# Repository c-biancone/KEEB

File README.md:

# KEEB

SOLIDWORKS and KiCAD fiels for a custom keyboard I hope to build.

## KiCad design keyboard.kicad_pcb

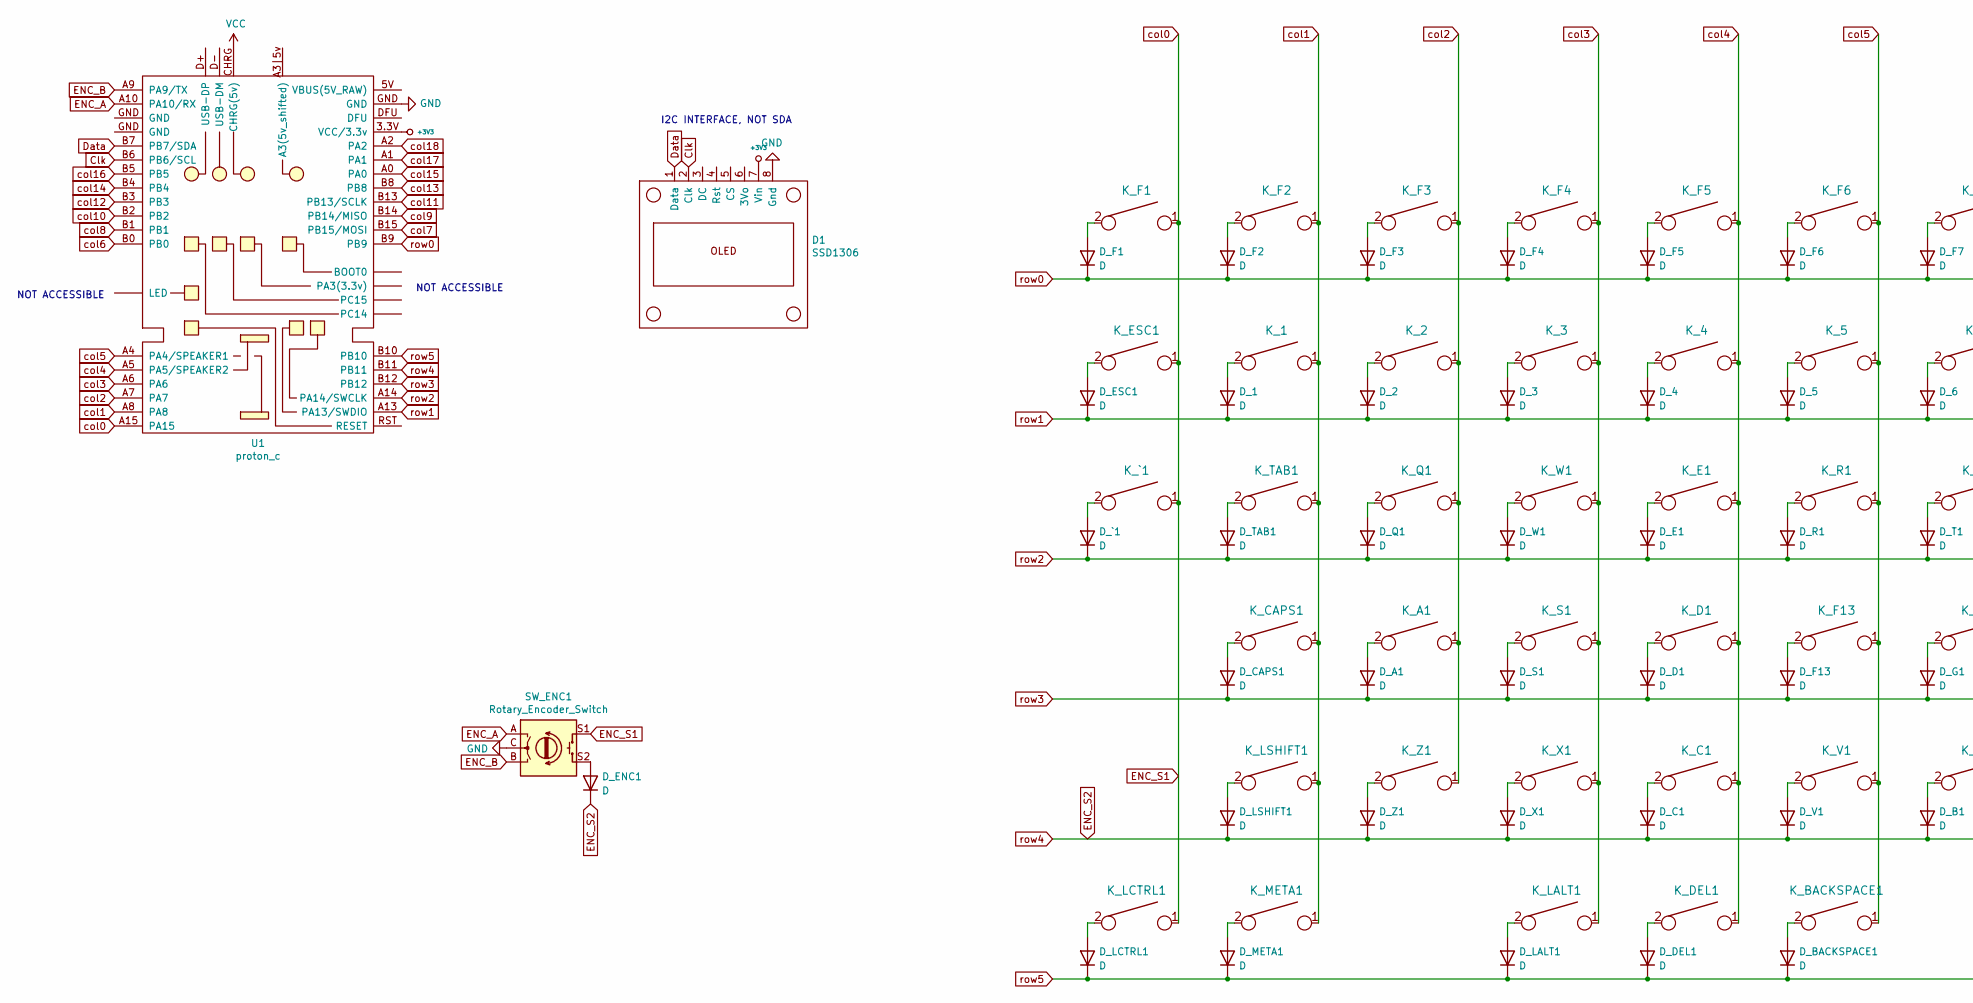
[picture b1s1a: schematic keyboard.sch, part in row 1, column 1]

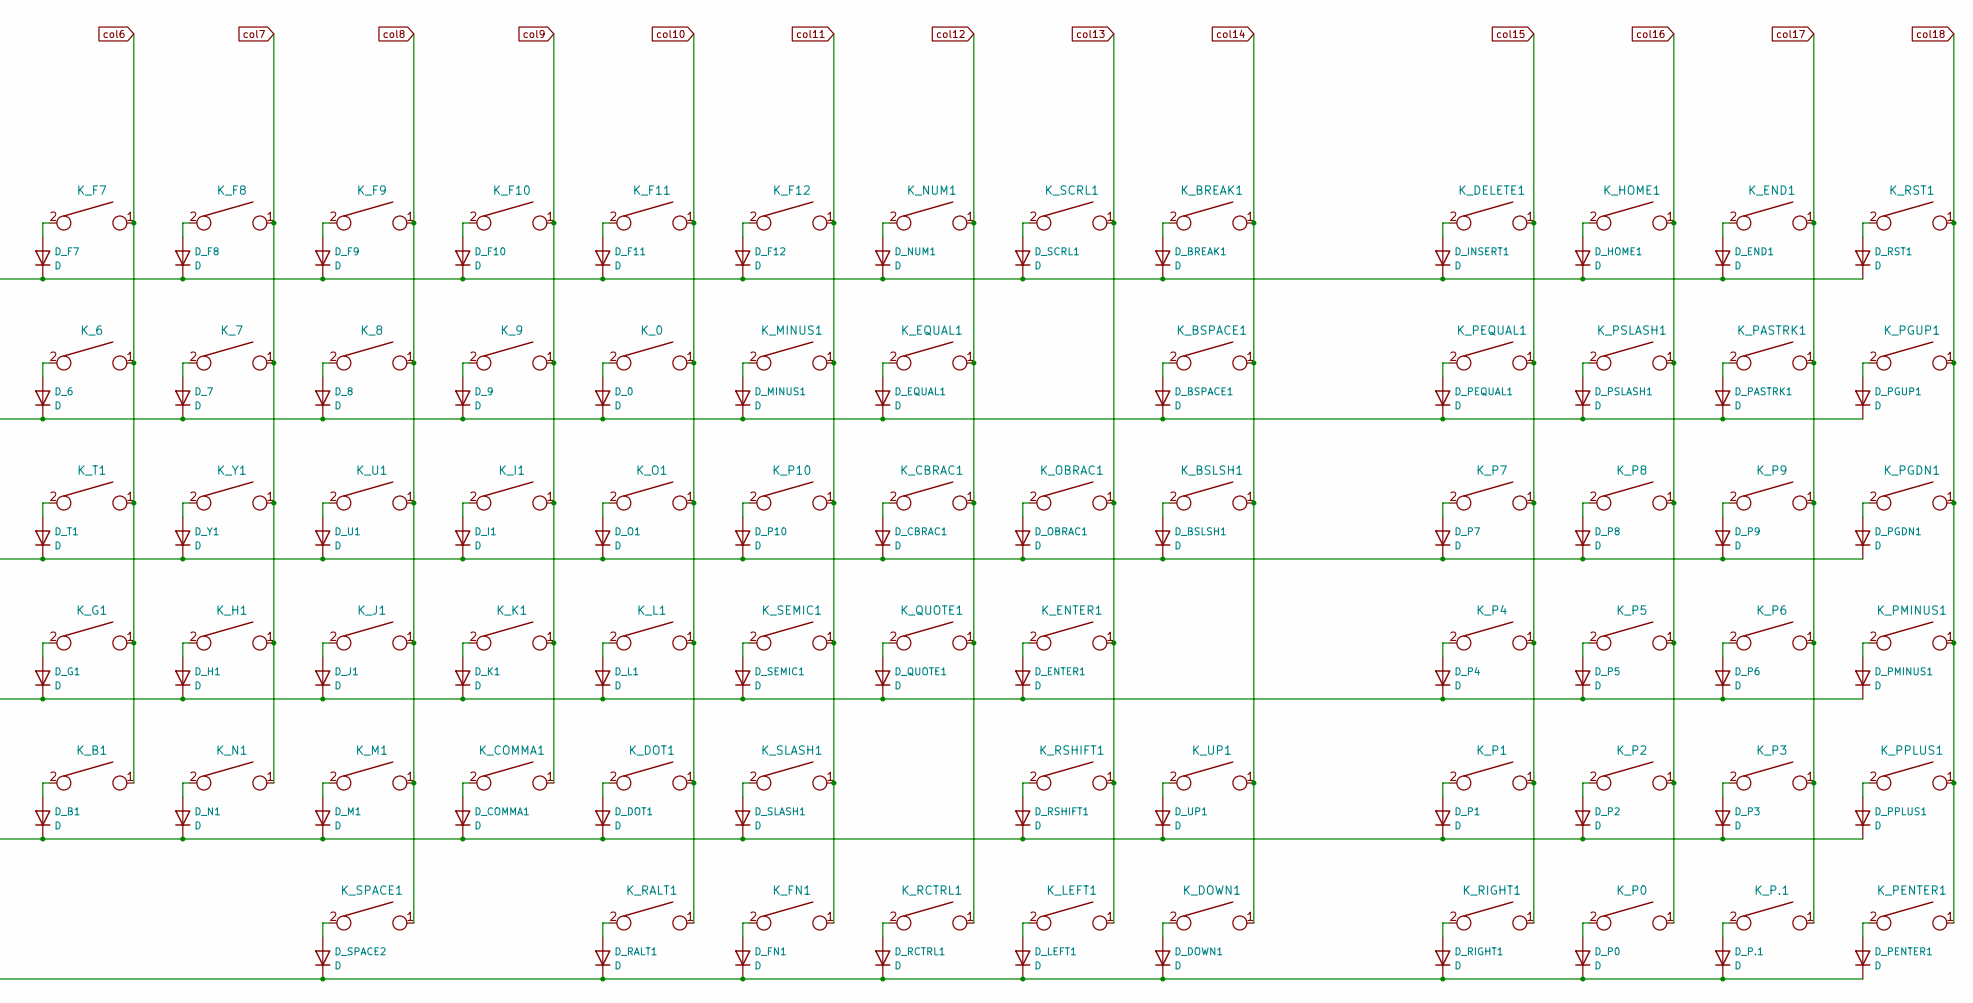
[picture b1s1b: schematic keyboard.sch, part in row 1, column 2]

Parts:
D1: SSD1306; MOUNTINGHOLE_2.5_PLATED
D_0, D_1, D_2, D_3, D_4, D_5, D_6, D_7, D_8, D_9: D; D_SOD123_axial
D_A1: D; D_SOD123_axial
D_B1: D; D_SOD123_axial
D_BACKSPACE1: D; D_SOD123_axial
D_BREAK1: D; D_SOD123_axial
D_BSLSH1: D; D_SOD123_axial
D_BSPACE1: D; D_SOD123_axial
D_C1: D; D_SOD123_axial
D_CAPS1: D; D_SOD123_axial
D_CBRAC1: D; D_SOD123_axial
D_COMMA1: D; D_SOD123_axial
D_D1: D; D_SOD123_axial
D_DEL1: D; D_SOD123_axial
D_DOT1: D; D_SOD123_axial
D_DOWN1: D; D_SOD123_axial
D_E1: D; D_SOD123_axial
D_ENC1: D; D_SOD123_axial
D_END1: D; D_SOD123_axial
D_ENTER1: D; D_SOD123_axial
D_EQUAL1: D; D_SOD123_axial
D_ESC1: D; D_SOD123_axial
D_F1, D_F2, D_F3, D_F4, D_F5, D_F6, D_F7, D_F8, D_F9, D_F10, D_F11, D_F12, D_F13: D; D_SOD123_axial
D_FN1: D; D_SOD123_axial
D_G1: D; D_SOD123_axial
D_H1: D; D_SOD123_axial
D_HOME1: D; D_SOD123_axial
D_I1: D; D_SOD123_axial
D_INSERT1: D; D_SOD123_axial
D_J1: D; D_SOD123_axial
D_K1: D; D_SOD123_axial
D_L1: D; D_SOD123_axial
D_LALT1: D; D_SOD123_axial
D_LCTRL1: D; D_SOD123_axial
D_LEFT1: D; D_SOD123_axial
D_LSHIFT1: D; D_SOD123_axial
D_M1: D; D_SOD123_axial
D_META1: D; D_SOD123_axial
D_MINUS1: D; D_SOD123_axial
D_N1: D; D_SOD123_axial
D_NUM1: D; D_SOD123_axial
D_O1: D; D_SOD123_axial
D_OBRAC1: D; D_SOD123_axial
D_P0, D_P1, D_P2, D_P3, D_P4, D_P5, D_P6, D_P7, D_P8, D_P9, D_P10, D_P.1: D; D_SOD123_axial
D_PASTRK1: D; D_SOD123_axial
D_PENTER1: D; D_SOD123_axial
D_PEQUAL1: D; D_SOD123_axial
D_PGDN1: D; D_SOD123_axial
D_PGUP1: D; D_SOD123_axial
D_PMINUS1: D; D_SOD123_axial
D_PPLUS1: D; D_SOD123_axial
D_PSLASH1: D; D_SOD123_axial
D_Q1: D; D_SOD123_axial
D_QUOTE1: D; D_SOD123_axial
D_R1: D; D_SOD123_axial
D_RALT1: D; D_SOD123_axial
D_RCTRL1: D; D_SOD123_axial
D_RIGHT1: D; D_SOD123_axial
D_RSHIFT1: D; D_SOD123_axial
D_RST1: D; D_SOD123_axial
D_S1: D; D_SOD123_axial
D_SCRL1: D; D_SOD123_axial
D_SEMIC1: D; D_SOD123_axial
D_SLASH1: D; D_SOD123_axial
D_SPACE2: D; D_SOD123_axial
D_T1: D; D_SOD123_axial
D_TAB1: D; D_SOD123_axial
D_U1: D; D_SOD123_axial
D_UP1: D; D_SOD123_axial
D_V1: D; D_SOD123_axial
D_W1: D; D_SOD123_axial
D_X1: D; D_SOD123_axial
D_Y1: D; D_SOD123_axial
D_Z1: D; D_SOD123_axial
D_`1: D; D_SOD123_axial
K_0, K_1, K_2, K_3, K_4, K_5, K_6, K_7, K_8, K_9: KEYSW; MX-1U-NoLED
K_A1: KEYSW; MX-1U-NoLED
K_B1: KEYSW; MX-1U-NoLED
K_BACKSPACE1: KEYSW; MX-2U-NoLED
K_BREAK1: KEYSW; MX-1U-NoLED
K_BSLSH1: KEYSW; MX-1.5U-NoLED
K_BSPACE1: KEYSW; MX-2U-NoLED
K_C1: KEYSW; MX-1U-NoLED
K_CAPS1: KEYSW; MX-1.75U-NoLED
K_CBRAC1: KEYSW; MX-1U-NoLED
K_COMMA1: KEYSW; MX-1U-NoLED
K_D1: KEYSW; MX-1U-NoLED
K_DEL1: KEYSW; MX-1U-NoLED
K_DELETE1: KEYSW; MX-1U-NoLED
K_DOT1: KEYSW; MX-1U-NoLED
K_DOWN1: KEYSW; MX-1U-NoLED
K_E1: KEYSW; MX-1U-NoLED
K_END1: KEYSW; MX-1U-NoLED
K_ENTER1: KEYSW; MX-2.25U-NoLED
K_EQUAL1: KEYSW; MX-1U-NoLED
K_ESC1: KEYSW; MX-1U-NoLED
K_F1, K_F2, K_F3, K_F4, K_F5, K_F6, K_F7, K_F8, K_F9, K_F10, K_F11, K_F12, K_F13: KEYSW; MX-1U-NoLED
K_FN1: KEYSW; MX-1.25U-NoLED
K_G1: KEYSW; MX-1U-NoLED
K_H1: KEYSW; MX-1U-NoLED
K_HOME1: KEYSW; MX-1U-NoLED
K_I1: KEYSW; MX-1U-NoLED
K_J1: KEYSW; MX-1U-NoLED
K_K1: KEYSW; MX-1U-NoLED
K_L1: KEYSW; MX-1U-NoLED
K_LALT1: KEYSW; MX-1.25U-NoLED
K_LCTRL1: KEYSW; MX-1.25U-NoLED
K_LEFT1: KEYSW; MX-1U-NoLED
K_LSHIFT1: KEYSW; MX-2.25U-NoLED
K_M1: KEYSW; MX-1U-NoLED
K_META1: KEYSW; MX-1.25U-NoLED
K_MINUS1: KEYSW; MX-1U-NoLED
K_N1: KEYSW; MX-1U-NoLED
K_NUM1: KEYSW; MX-1U-NoLED
K_O1: KEYSW; MX-1U-NoLED
K_OBRAC1: KEYSW; MX-1U-NoLED
K_P0, K_P1, K_P2, K_P3, K_P4, K_P5, K_P6, K_P7, K_P8, K_P9, K_P10, K_P.1: KEYSW; MX-1U-NoLED
K_PASTRK1: KEYSW; MX-1U-NoLED
K_PENTER1: KEYSW; MX-2U-NoLED
K_PEQUAL1: KEYSW; MX-1U-NoLED
K_PGDN1: KEYSW; MX-1U-NoLED
K_PGUP1: KEYSW; MX-1U-NoLED
K_PMINUS1: KEYSW; MX-1U-NoLED
K_PPLUS1: KEYSW; MX-1U-NoLED
K_PSLASH1: KEYSW; MX-1U-NoLED
K_Q1: KEYSW; MX-1U-NoLED
K_QUOTE1: KEYSW; MX-1U-NoLED
K_R1: KEYSW; MX-1U-NoLED
K_RALT1: KEYSW; MX-1U-NoLED
K_RCTRL1: KEYSW; MX-1.25U-NoLED
K_RIGHT1: KEYSW; MX-1U-NoLED
K_RSHIFT1: KEYSW; MX-1.75U-NoLED
K_RST1: KEYSW; MX-1U-NoLED
K_S1: KEYSW; MX-1U-NoLED
K_SCRL1: KEYSW; MX-1U-NoLED
K_SEMIC1: KEYSW; MX-1U-NoLED
K_SLASH1: KEYSW; MX-1U-NoLED
K_SPACE1: KEYSW; MX-2.75U-NoLED
K_T1: KEYSW; MX-1U-NoLED
K_TAB1: KEYSW; MX-1.5U-NoLED
K_U1: KEYSW; MX-1U-NoLED
K_UP1: KEYSW; MX-1U-NoLED
K_V1: KEYSW; MX-1U-NoLED
K_W1: KEYSW; MX-1U-NoLED
K_X1: KEYSW; MX-1U-NoLED
K_Y1: KEYSW; MX-1U-NoLED
K_Z1: KEYSW; MX-1U-NoLED
K_`1: KEYSW; MX-1U-NoLED
SW_ENC1: Rotary_Encoder_Switch; RotaryEncoder_Alps_EC11E-Switch_Vertical_H20mm
U1: proton_c

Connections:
+5V: D1.7 (Vin), U1.3.3V (VCC/3.3v)
Clk: D1.2 (Clk), U1.B6 (PB6/SCL)
Data: D1.1 (Data), U1.B7 (PB7/SDA)
ENC_A: SW_ENC1.A, U1.A10 (PA10/RX)
ENC_B: SW_ENC1.B, U1.A9 (PA9/TX)
ENC_S1: K_ESC1.1, K_F1.1, K_LCTRL1.1, K_`1.1, SW_ENC1.S1, U1.A15
ENC_S2: D_B1.1 (K), D_C1.1 (K), D_COMMA1.1 (K), D_DOT1.1 (K), D_ENC1.1 (K), D_LSHIFT1.1 (K), D_M1.1 (K), D_N1.1 (K), D_P1.1 (K), D_P2.1 (K), D_P3.1 (K), D_PPLUS1.1 (K), D_RSHIFT1.1 (K), D_SLASH1.1 (K), D_UP1.1 (K), D_V1.1 (K), D_X1.1 (K), D_Z1.1 (K), U1.B11
GND: D1.8 (Gnd), SW_ENC1.C, U1.GND
unnamed: D_0.2 (A), K_0.2
unnamed: D_1.2 (A), K_1.2
unnamed: D_2.2 (A), K_2.2
unnamed: D_3.2 (A), K_3.2
unnamed: D_4.2 (A), K_4.2
unnamed: D_5.2 (A), K_5.2
unnamed: D_6.2 (A), K_6.2
unnamed: D_7.2 (A), K_7.2
unnamed: D_8.2 (A), K_8.2
unnamed: D_9.2 (A), K_9.2
unnamed: D_A1.2 (A), K_A1.2
unnamed: D_B1.2 (A), K_B1.2
unnamed: D_BACKSPACE1.2 (A), K_BACKSPACE1.2
unnamed: D_BREAK1.2 (A), K_BREAK1.2
unnamed: D_BSLSH1.2 (A), K_BSLSH1.2
unnamed: D_BSPACE1.2 (A), K_BSPACE1.2
unnamed: D_C1.2 (A), K_C1.2
unnamed: D_CAPS1.2 (A), K_CAPS1.2
unnamed: D_CBRAC1.2 (A), K_CBRAC1.2
unnamed: D_COMMA1.2 (A), K_COMMA1.2
unnamed: D_D1.2 (A), K_D1.2
unnamed: D_DEL1.2 (A), K_DEL1.2
unnamed: D_DOT1.2 (A), K_DOT1.2
unnamed: D_DOWN1.2 (A), K_DOWN1.2
unnamed: D_E1.2 (A), K_E1.2
unnamed: D_ENC1.2 (A), SW_ENC1.S2
unnamed: D_END1.2 (A), K_END1.2
unnamed: D_ENTER1.2 (A), K_ENTER1.2
unnamed: D_EQUAL1.2 (A), K_EQUAL1.2
unnamed: D_ESC1.2 (A), K_ESC1.2
unnamed: D_F1.2 (A), K_F1.2
unnamed: D_F2.2 (A), K_F2.2
unnamed: D_F3.2 (A), K_F3.2
unnamed: D_F4.2 (A), K_F4.2
unnamed: D_F5.2 (A), K_F5.2
unnamed: D_F6.2 (A), K_F6.2
unnamed: D_F7.2 (A), K_F7.2
unnamed: D_F8.2 (A), K_F8.2
unnamed: D_F9.2 (A), K_F9.2
unnamed: D_F10.2 (A), K_F10.2
unnamed: D_F11.2 (A), K_F11.2
unnamed: D_F12.2 (A), K_F12.2
unnamed: D_F13.2 (A), K_F13.2
unnamed: D_FN1.2 (A), K_FN1.2
unnamed: D_G1.2 (A), K_G1.2
unnamed: D_H1.2 (A), K_H1.2
unnamed: D_HOME1.2 (A), K_HOME1.2
unnamed: D_I1.2 (A), K_I1.2
unnamed: D_INSERT1.2 (A), K_DELETE1.2
unnamed: D_J1.2 (A), K_J1.2
unnamed: D_K1.2 (A), K_K1.2
unnamed: D_L1.2 (A), K_L1.2
unnamed: D_LALT1.2 (A), K_LALT1.2
unnamed: D_LCTRL1.2 (A), K_LCTRL1.2
unnamed: D_LEFT1.2 (A), K_LEFT1.2
unnamed: D_LSHIFT1.2 (A), K_LSHIFT1.2
unnamed: D_M1.2 (A), K_M1.2
unnamed: D_META1.2 (A), K_META1.2
unnamed: D_MINUS1.2 (A), K_MINUS1.2
unnamed: D_N1.2 (A), K_N1.2
unnamed: D_NUM1.2 (A), K_NUM1.2
unnamed: D_O1.2 (A), K_O1.2
unnamed: D_OBRAC1.2 (A), K_OBRAC1.2
unnamed: D_P0.2 (A), K_P0.2
unnamed: D_P1.2 (A), K_P1.2
unnamed: D_P2.2 (A), K_P2.2
unnamed: D_P3.2 (A), K_P3.2
unnamed: D_P4.2 (A), K_P4.2
unnamed: D_P5.2 (A), K_P5.2
unnamed: D_P6.2 (A), K_P6.2
unnamed: D_P7.2 (A), K_P7.2
unnamed: D_P8.2 (A), K_P8.2
unnamed: D_P9.2 (A), K_P9.2
unnamed: D_P10.2 (A), K_P10.2
unnamed: D_P.1.2 (A), K_P.1.2
unnamed: D_PASTRK1.2 (A), K_PASTRK1.2
unnamed: D_PENTER1.2 (A), K_PENTER1.2
unnamed: D_PEQUAL1.2 (A), K_PEQUAL1.2
unnamed: D_PGDN1.2 (A), K_PGDN1.2
unnamed: D_PGUP1.2 (A), K_PGUP1.2
unnamed: D_PMINUS1.2 (A), K_PMINUS1.2
unnamed: D_PPLUS1.2 (A), K_PPLUS1.2
unnamed: D_PSLASH1.2 (A), K_PSLASH1.2
unnamed: D_Q1.2 (A), K_Q1.2
unnamed: D_QUOTE1.2 (A), K_QUOTE1.2
unnamed: D_R1.2 (A), K_R1.2
unnamed: D_RALT1.2 (A), K_RALT1.2
unnamed: D_RCTRL1.2 (A), K_RCTRL1.2
unnamed: D_RIGHT1.2 (A), K_RIGHT1.2
unnamed: D_RSHIFT1.2 (A), K_RSHIFT1.2
unnamed: D_RST1.2 (A), K_RST1.2
unnamed: D_S1.2 (A), K_S1.2
unnamed: D_SCRL1.2 (A), K_SCRL1.2
unnamed: D_SEMIC1.2 (A), K_SEMIC1.2
unnamed: D_SLASH1.2 (A), K_SLASH1.2
unnamed: D_SPACE2.2 (A), K_SPACE1.2
unnamed: D_T1.2 (A), K_T1.2
unnamed: D_TAB1.2 (A), K_TAB1.2
unnamed: D_U1.2 (A), K_U1.2
unnamed: D_UP1.2 (A), K_UP1.2
unnamed: D_V1.2 (A), K_V1.2
unnamed: D_W1.2 (A), K_W1.2
unnamed: D_X1.2 (A), K_X1.2
unnamed: D_Y1.2 (A), K_Y1.2
unnamed: D_Z1.2 (A), K_Z1.2
unnamed: D_`1.2 (A), K_`1.2
VCC: U1.CHRG (CHRG(5v))
col1: K_1.1, K_CAPS1.1, K_F2.1, K_LSHIFT1.1, K_META1.1, K_TAB1.1, U1.A8
col2: K_2.1, K_A1.1, K_F3.1, K_Q1.1, K_Z1.1, U1.A7
col3: K_3.1, K_F4.1, K_LALT1.1, K_S1.1, K_W1.1, K_X1.1, U1.A6
col4: K_4.1, K_C1.1, K_D1.1, K_DEL1.1, K_E1.1, K_F5.1, U1.A5 (PA5/SPEAKER2)
col5: K_5.1, K_BACKSPACE1.1, K_F6.1, K_F13.1, K_R1.1, K_V1.1, U1.A4 (PA4/SPEAKER1)
col6: K_6.1, K_B1.1, K_F7.1, K_G1.1, K_T1.1, U1.B0
col7: K_7.1, K_F8.1, K_H1.1, K_N1.1, K_Y1.1, U1.B15 (PB15/MOSI)
col8: K_8.1, K_F9.1, K_J1.1, K_M1.1, K_SPACE1.1, K_U1.1, U1.B1
col9: K_9.1, K_COMMA1.1, K_F10.1, K_I1.1, K_K1.1, U1.B14 (PB14/MISO)
col10: K_0.1, K_DOT1.1, K_F11.1, K_L1.1, K_O1.1, K_RALT1.1, U1.B2
col11: K_F12.1, K_FN1.1, K_MINUS1.1, K_P10.1, K_SEMIC1.1, K_SLASH1.1, U1.B13 (PB13/SCLK)
col12: K_CBRAC1.1, K_EQUAL1.1, K_NUM1.1, K_QUOTE1.1, K_RCTRL1.1, U1.B3
col13: K_ENTER1.1, K_LEFT1.1, K_OBRAC1.1, K_RSHIFT1.1, K_SCRL1.1, U1.B8
col14: K_BREAK1.1, K_BSLSH1.1, K_BSPACE1.1, K_DOWN1.1, K_UP1.1, U1.B4
col15: K_DELETE1.1, K_P1.1, K_P4.1, K_P7.1, K_PEQUAL1.1, K_RIGHT1.1, U1.A0
col16: K_HOME1.1, K_P0.1, K_P2.1, K_P5.1, K_P8.1, K_PSLASH1.1, U1.B5
col17: K_END1.1, K_P3.1, K_P6.1, K_P9.1, K_P.1.1, K_PASTRK1.1, U1.A1
col18: K_PENTER1.1, K_PGDN1.1, K_PGUP1.1, K_PMINUS1.1, K_PPLUS1.1, K_RST1.1, U1.A2
row0: D_BREAK1.1 (K), D_END1.1 (K), D_F1.1 (K), D_F2.1 (K), D_F3.1 (K), D_F4.1 (K), D_F5.1 (K), D_F6.1 (K), D_F7.1 (K), D_F8.1 (K), D_F9.1 (K), D_F10.1 (K), D_F11.1 (K), D_F12.1 (K), D_HOME1.1 (K), D_INSERT1.1 (K), D_NUM1.1 (K), D_RST1.1 (K), D_SCRL1.1 (K), U1.B9
row1: D_0.1 (K), D_1.1 (K), D_2.1 (K), D_3.1 (K), D_4.1 (K), D_5.1 (K), D_6.1 (K), D_7.1 (K), D_8.1 (K), D_9.1 (K), D_BSPACE1.1 (K), D_EQUAL1.1 (K), D_ESC1.1 (K), D_MINUS1.1 (K), D_PASTRK1.1 (K), D_PEQUAL1.1 (K), D_PGUP1.1 (K), D_PSLASH1.1 (K), U1.A13 (PA13/SWDIO)
row2: D_BSLSH1.1 (K), D_CBRAC1.1 (K), D_E1.1 (K), D_I1.1 (K), D_O1.1 (K), D_OBRAC1.1 (K), D_P7.1 (K), D_P8.1 (K), D_P9.1 (K), D_P10.1 (K), D_PGDN1.1 (K), D_Q1.1 (K), D_R1.1 (K), D_T1.1 (K), D_TAB1.1 (K), D_U1.1 (K), D_W1.1 (K), D_Y1.1 (K), D_`1.1 (K), U1.A14 (PA14/SWCLK)
row3: D_A1.1 (K), D_CAPS1.1 (K), D_D1.1 (K), D_ENTER1.1 (K), D_F13.1 (K), D_G1.1 (K), D_H1.1 (K), D_J1.1 (K), D_K1.1 (K), D_L1.1 (K), D_P4.1 (K), D_P5.1 (K), D_P6.1 (K), D_PMINUS1.1 (K), D_QUOTE1.1 (K), D_S1.1 (K), D_SEMIC1.1 (K), U1.B12
row5: D_BACKSPACE1.1 (K), D_DEL1.1 (K), D_DOWN1.1 (K), D_FN1.1 (K), D_LALT1.1 (K), D_LCTRL1.1 (K), D_LEFT1.1 (K), D_META1.1 (K), D_P0.1 (K), D_P.1.1 (K), D_PENTER1.1 (K), D_RALT1.1 (K), D_RCTRL1.1 (K), D_RIGHT1.1 (K), D_SPACE2.1 (K), U1.B10

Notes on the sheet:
I2C INTERFACE, NOT SDA
NOT ACCESSIBLE

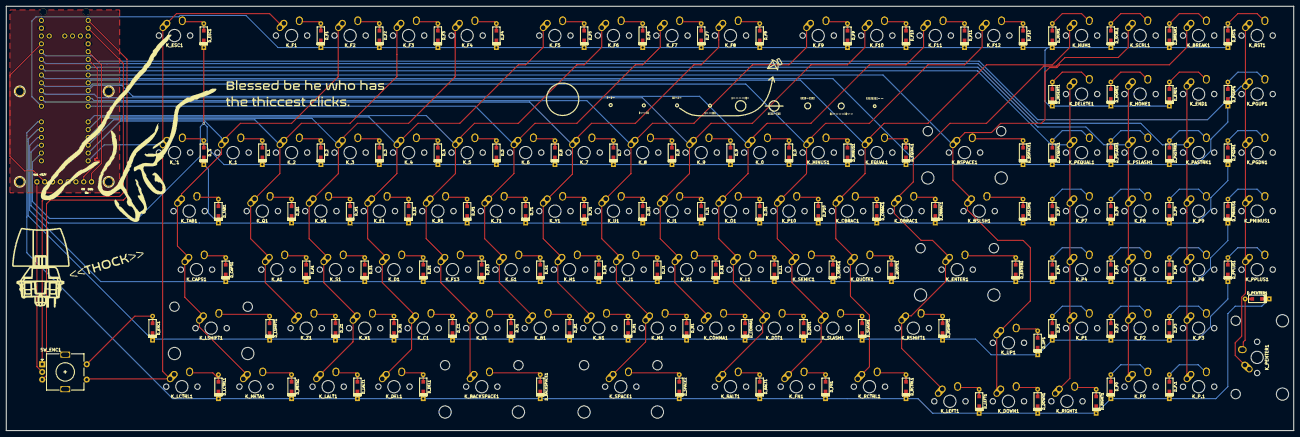
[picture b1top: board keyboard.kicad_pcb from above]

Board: 2 copper layers, 419.1 x 138.1 mm, 214 parts (1 on the bottom side), 137 nets.

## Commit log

2021-01-21 remove other repo
